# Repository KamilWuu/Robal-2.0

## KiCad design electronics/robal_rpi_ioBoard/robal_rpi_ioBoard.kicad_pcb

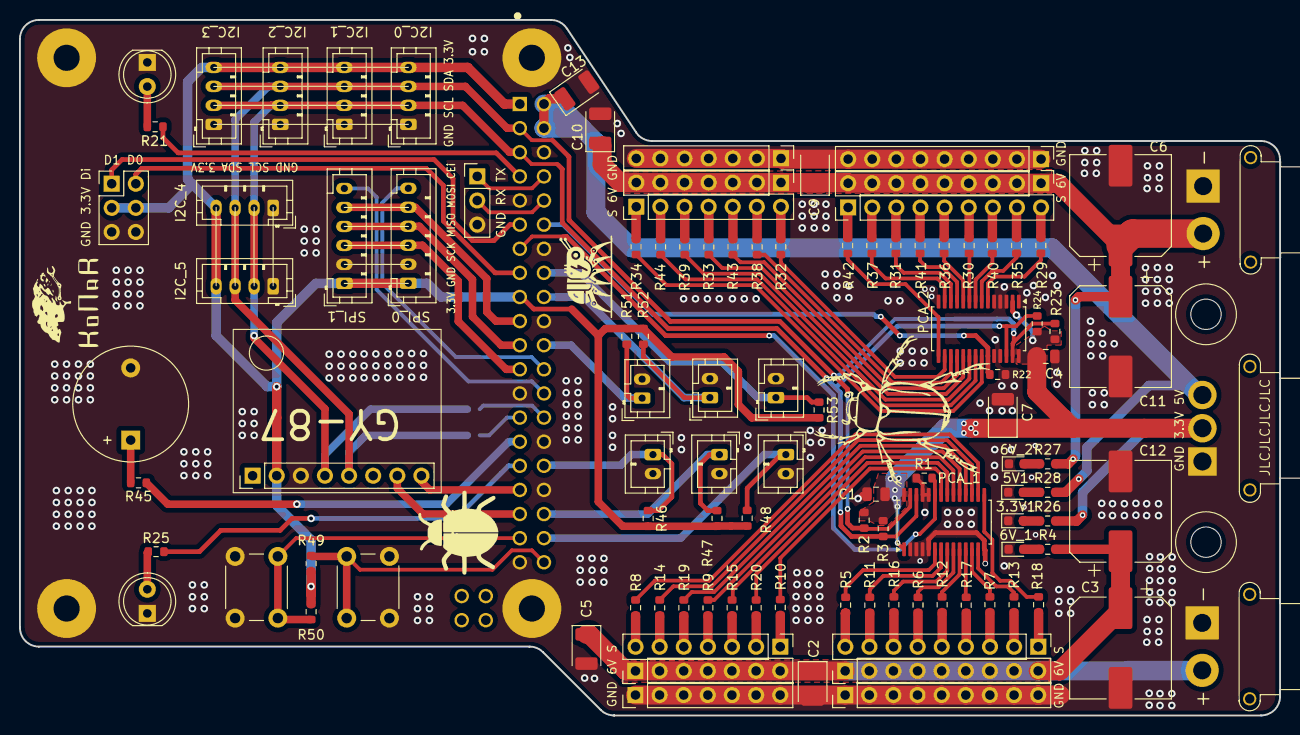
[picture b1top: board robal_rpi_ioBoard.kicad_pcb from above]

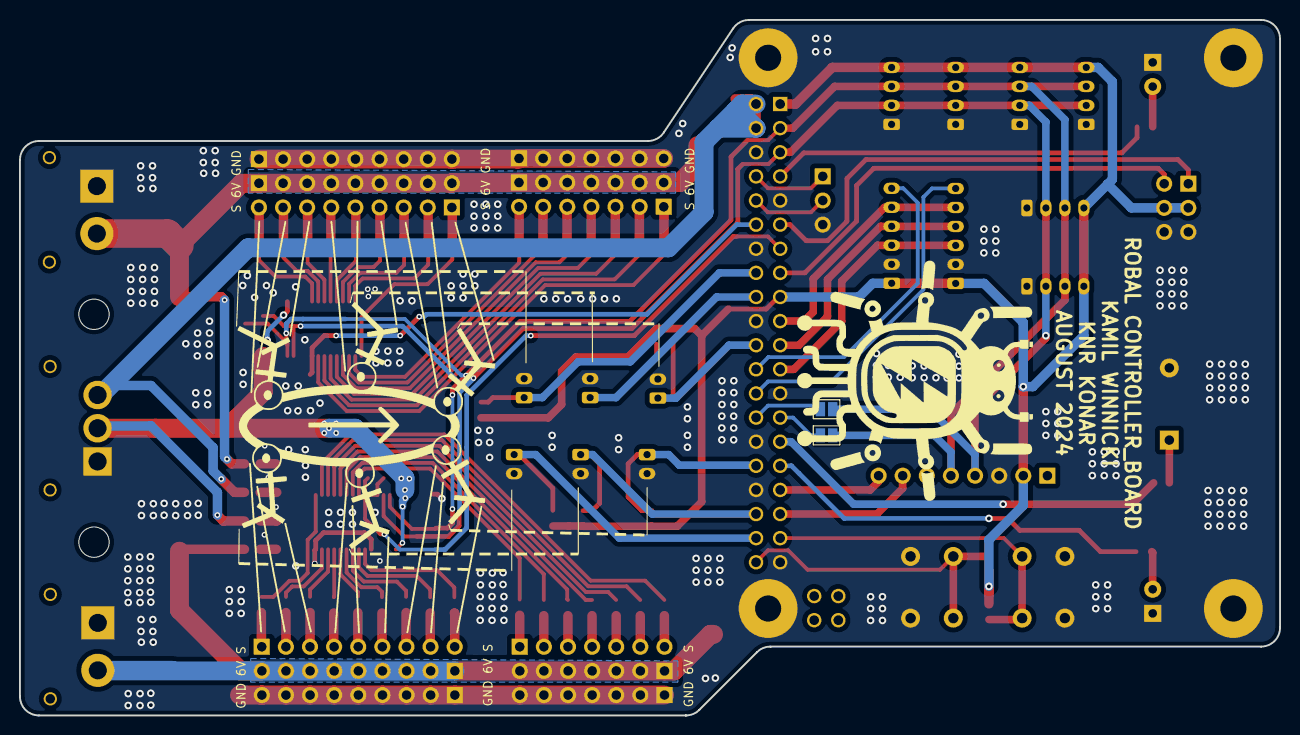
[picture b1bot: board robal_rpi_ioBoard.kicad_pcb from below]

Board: 2 copper layers, 132.7 x 73.2 mm, 111 parts (2 on the bottom side), 105 nets.

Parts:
3.3V1, 5V1, 6V_1, 6V_2: LED; LED_0603_1608Metric
BZ1: Buzzer; Buzzer_12x9.5RM7.6
C1, C4: 10uF; C_0805_2012Metric
C2, C5, C7, C9, C10, C13: >1mF; CP_EIA-3528-21_Kemet-B
C3, C6, C11, C12: >1mF; CP_Elec_10x10.5
D2, D7: LED; LED_D5.0mm
GY-87: GY-87
J1: Conn_01x03_Pin; PinHeader_1x03_P2.54mm_Vertical
J2, J3: Conn_01x02_Socket; AMASS_XT30PW-F_1x02_P2.50mm_Horizontal
J4: Conn_01x03_Socket; AMASS_MR30PW-FB_1x03_P3.50mm_Horizontal
J5, J6, J7, J8, J10, J11: Conn_01x04_Socket; JST_PH_B4B-PH-K_1x04_P2.00mm_Vertical
J9: Conn_02x03_Counter_Clockwise; PinHeader_2x03_P2.54mm_Vertical
JP1, JP2: Jumper_2_Open; SolderJumper-2_P1.3mm_Open_Pad1.0x1.5mm
PCA_1, PCA_2: PCA9685PW; TSSOP-28_4.4x9.7mm_P0.65mm
PCA_1_G_CONN1: PCA_1_G1; PinHeader_1x09_P2.54mm_Vertical
PCA_1_G_CONN2: PCA_1_G2; PinHeader_1x07_P2.54mm_Vertical
PCA_1_S_CONN1: PCA_1_S1; PinHeader_1x09_P2.54mm_Vertical
PCA_1_S_CONN2: PCA_1_S2; PinHeader_1x07_P2.54mm_Vertical
PCA_1_V_CONN1: PCA_1_V1; PinHeader_1x09_P2.54mm_Vertical
PCA_1_V_CONN2: PCA_1_V2; PinHeader_1x07_P2.54mm_Vertical
PCA_2_G_CONN1: PCA_2_G1; PinHeader_1x09_P2.54mm_Vertical
PCA_2_G_CONN2: PCA_2_G2; PinHeader_1x07_P2.54mm_Vertical
PCA_2_S_CONN1: PCA_2_S1; PinHeader_1x09_P2.54mm_Vertical
PCA_2_S_CONN2: PCA_2_S2; PinHeader_1x07_P2.54mm_Vertical
PCA_2_V_CONN1: PCA_2_V1; PinHeader_1x09_P2.54mm_Vertical
PCA_2_V_CONN2: PCA_2_V2; PinHeader_1x07_P2.54mm_Vertical
R1, R2, R3, R22, R23, R24, R46, R47, R48, R49, R50, R51, R52, R53: 10K; R_0603_1608Metric
R4, R27: 2K; R_0603_1608Metric
R5, R6, R7, R8, R9, R10, R11, R12, R13, R14, R15, R16, R17, R18, R19, R20, R29, R30, R31, R32, R33, R34, R35, R36, R37, R38, R39, R40, R41, R42, R43, R44: 220; R_0603_1608Metric
R21, R25, R26, R28: 500; R_0603_1608Metric
R45: 1K; R_0603_1608Metric
SPI_CONN0, SPI_CONN1: SPI_CONN; JST_PH_B6B-PH-K_1x06_P2.00mm_Vertical
SW1, SW2: SW_Omron_B3FS; SW_PUSH_6mm
TS_1, TS_2, TS_3, TS_4, TS_5, TS_6: TS_socket; JST_PH_B2B-PH-K_1x02_P2.00mm_Vertical
U1: RASPBERRY_PI_4B_4GB; MODULE_RASPBERRY_PI_4B_4GB

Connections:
+3.3V: C1.1, C4.1, C7.1, J4.2, PCA_1.1 (A0), PCA_1.28 (VDD), PCA_2.2 (A1), PCA_2.28 (VDD), R2.2, R3.1, R23.2, R24.1, R26.2
+3.3V_RP: GY-87.2 (3.3V), J5.4, J6.4, J7.4, J8.4, J9.3, J9.4, J10.4, J11.4, R46.2, R47.2, R48.2, R49.1, R50.1, R51.2, R52.2, R53.2, SPI_CONN0.1, SPI_CONN1.1, U1.1 (3V3), U1.17 (3V3)
+5V: C13.1, J4.3, R28.2, U1.2 (5V), U1.4 (5V)
+6V_1: C2.1, C3.1, C5.1, C12.1, J2.2, PCA_1_V_CONN1.1, PCA_1_V_CONN1.2, PCA_1_V_CONN1.3, PCA_1_V_CONN1.4, PCA_1_V_CONN1.5, PCA_1_V_CONN1.6, PCA_1_V_CONN1.7, PCA_1_V_CONN1.8, PCA_1_V_CONN1.9, PCA_1_V_CONN2.1, PCA_1_V_CONN2.2, PCA_1_V_CONN2.3, PCA_1_V_CONN2.4, PCA_1_V_CONN2.5, PCA_1_V_CONN2.6, PCA_1_V_CONN2.7, R4.2
+6V_2: C6.1, C9.1, C10.1, C11.1, J3.2, PCA_2_V_CONN1.1, PCA_2_V_CONN1.2, PCA_2_V_CONN1.3, PCA_2_V_CONN1.4, PCA_2_V_CONN1.5, PCA_2_V_CONN1.6, PCA_2_V_CONN1.7, PCA_2_V_CONN1.8, PCA_2_V_CONN1.9, PCA_2_V_CONN2.1, PCA_2_V_CONN2.2, PCA_2_V_CONN2.3, PCA_2_V_CONN2.4, PCA_2_V_CONN2.5, PCA_2_V_CONN2.6, PCA_2_V_CONN2.7, R27.2
BUZZ: R45.1, U1.29 (GPIO5)
D0: J9.2, U1.15 (GPIO22/GPIO_GEN3)
D1: J9.1, U1.11 (GPIO17/GPIO_GEN0)
DRDY: GY-87.8 (DRDY), U1.33 (GPIO13)
GND: 3.3V1.1 (K), 5V1.1 (K), 6V_1.1 (K), 6V_2.1 (K), BZ1.2 (-), C1.2, C2.2, C3.2, C4.2, C5.2, C6.2, C7.2, C9.2, C10.2, C11.2, C12.2, C13.2, D2.1 (K), D7.1 (K), GY-87.3 (GND), J1.3, J2.1, J3.1, J4.1, J5.1, J6.1, J7.1, J8.1, J9.5, J9.6, J10.1, J11.1, PCA_1.2 (A1), PCA_1.3 (A2), PCA_1.4 (A3), PCA_1.5 (A4), PCA_1.14 (VSS), PCA_1.24 (A5), PCA_1.25 (EXTCLK), PCA_1_G_CONN1.1, PCA_1_G_CONN1.2, PCA_1_G_CONN1.3, PCA_1_G_CONN1.4, PCA_1_G_CONN1.5, PCA_1_G_CONN1.6, PCA_1_G_CONN1.7, PCA_1_G_CONN1.8, PCA_1_G_CONN1.9, PCA_1_G_CONN2.1, PCA_1_G_CONN2.2, PCA_1_G_CONN2.3, PCA_1_G_CONN2.4, PCA_1_G_CONN2.5, PCA_1_G_CONN2.6, PCA_1_G_CONN2.7, PCA_2.1 (A0), PCA_2.3 (A2), PCA_2.4 (A3), PCA_2.5 (A4), PCA_2.14 (VSS), PCA_2.24 (A5), PCA_2.25 (EXTCLK), PCA_2_G_CONN1.1, PCA_2_G_CONN1.2, PCA_2_G_CONN1.3, PCA_2_G_CONN1.4, PCA_2_G_CONN1.5, PCA_2_G_CONN1.6, PCA_2_G_CONN1.7, PCA_2_G_CONN1.8, PCA_2_G_CONN1.9, PCA_2_G_CONN2.1, PCA_2_G_CONN2.2, PCA_2_G_CONN2.3, PCA_2_G_CONN2.4, PCA_2_G_CONN2.5, PCA_2_G_CONN2.6, PCA_2_G_CONN2.7, R1.2, R22.2, SPI_CONN0.2, SPI_CONN1.2, SW1.2, SW2.2, TS_1.2, TS_2.2, TS_3.2, TS_4.2, TS_5.2, TS_6.2, U1.6 (GND), U1.9 (GND), U1.14 (GND), U1.20 (GND), U1.25 (GND), U1.30 (GND), U1.34 (GND), U1.39 (GND), U1.S1 (SHIELD), U1.S2 (SHIELD), U1.S3 (SHIELD), U1.S4 (SHIELD)
I2C_SCL: GY-87.4 (SCL), J5.2, J6.2, J7.2, J8.2, J10.2, J11.2, JP2.1 (A), PCA_1.26 (SCL), PCA_2.26 (SCL), R3.2, R24.2, U1.5 (GPIO3/SCL1)
I2C_SDA: GY-87.5 (SDA), J5.3, J6.3, J7.3, J8.3, J10.3, J11.3, JP1.1 (A), PCA_1.27 (SDA), PCA_2.27 (SDA), R2.1, R23.1, U1.3 (GPIO2/SDA1)
INTA_MPU: GY-87.7 (INTA), U1.35 (GPIO19)
unnamed: 3.3V1.2 (A), R26.1
unnamed: 5V1.2 (A), R28.1
unnamed: 6V_1.2 (A), R4.1
unnamed: 6V_2.2 (A), R27.1
unnamed: BZ1.1 (+), R45.2
unnamed: D2.2 (A), R21.1
unnamed: D7.2 (A), R25.1
unnamed: JP1.2 (B), U1.27 (ID_SD)
unnamed: JP2.2 (B), U1.28 (ID_SC)
unnamed: PCA_1.6 (LED0), R5.1
unnamed: PCA_1.7 (LED1), R11.1
unnamed: PCA_1.8 (LED2), R16.1
unnamed: PCA_1.9 (LED3), R6.1
unnamed: PCA_1.10 (LED4), R12.1
unnamed: PCA_1.11 (LED5), R17.1
unnamed: PCA_1.12 (LED6), R7.1
unnamed: PCA_1.13 (LED7), R13.1
unnamed: PCA_1.15 (LED8), R18.1
unnamed: PCA_1.16 (LED9), R8.1
unnamed: PCA_1.17 (LED10), R14.1
unnamed: PCA_1.18 (LED11), R19.1
unnamed: PCA_1.19 (LED12), R9.1
unnamed: PCA_1.20 (LED13), R15.1
unnamed: PCA_1.21 (LED14), R20.1
unnamed: PCA_1.22 (LED15), R10.1
unnamed: PCA_1_S_CONN1.1, R18.2
unnamed: PCA_1_S_CONN1.2, R13.2
unnamed: PCA_1_S_CONN1.3, R7.2
unnamed: PCA_1_S_CONN1.4, R17.2
unnamed: PCA_1_S_CONN1.5, R12.2
unnamed: PCA_1_S_CONN1.6, R6.2
unnamed: PCA_1_S_CONN1.7, R16.2
unnamed: PCA_1_S_CONN1.8, R11.2
unnamed: PCA_1_S_CONN1.9, R5.2
unnamed: PCA_1_S_CONN2.1, R10.2
unnamed: PCA_1_S_CONN2.2, R20.2
unnamed: PCA_1_S_CONN2.3, R15.2
unnamed: PCA_1_S_CONN2.4, R9.2
unnamed: PCA_1_S_CONN2.5, R19.2
unnamed: PCA_1_S_CONN2.6, R14.2
unnamed: PCA_1_S_CONN2.7, R8.2
unnamed: PCA_2.6 (LED0), R29.1
unnamed: PCA_2.7 (LED1), R35.1
unnamed: PCA_2.8 (LED2), R40.1
unnamed: PCA_2.9 (LED3), R30.1
unnamed: PCA_2.10 (LED4), R36.1
unnamed: PCA_2.11 (LED5), R41.1
unnamed: PCA_2.12 (LED6), R31.1
unnamed: PCA_2.13 (LED7), R37.1
unnamed: PCA_2.15 (LED8), R42.1
unnamed: PCA_2.16 (LED9), R32.1
unnamed: PCA_2.17 (LED10), R38.1
unnamed: PCA_2.18 (LED11), R43.1
unnamed: PCA_2.19 (LED12), R33.1
unnamed: PCA_2.20 (LED13), R39.1
unnamed: PCA_2.21 (LED14), R44.1
unnamed: PCA_2.22 (LED15), R34.1
unnamed: PCA_2_S_CONN1.1, R42.2
unnamed: PCA_2_S_CONN1.2, R37.2
unnamed: PCA_2_S_CONN1.3, R31.2
unnamed: PCA_2_S_CONN1.4, R41.2
unnamed: PCA_2_S_CONN1.5, R36.2
unnamed: PCA_2_S_CONN1.6, R30.2
unnamed: PCA_2_S_CONN1.7, R40.2
unnamed: PCA_2_S_CONN1.8, R35.2
unnamed: PCA_2_S_CONN1.9, R29.2
unnamed: PCA_2_S_CONN2.1, R34.2
unnamed: PCA_2_S_CONN2.2, R44.2
unnamed: PCA_2_S_CONN2.3, R39.2
unnamed: PCA_2_S_CONN2.4, R33.2
unnamed: PCA_2_S_CONN2.5, R43.2
unnamed: PCA_2_S_CONN2.6, R38.2
unnamed: PCA_2_S_CONN2.7, R32.2
PCA_1_OE: PCA_1.23 (~OE), R1.1, U1.13 (GPIO27/GPIO_GEN2)
PCA_2_OE: PCA_2.23 (~OE), R22.1, U1.12 (GPIO18/GPIO_GEN1)
SPI_CE0: SPI_CONN0.6, U1.24 (GPIO8/~SPI_CE0)
SPI_CE1: SPI_CONN1.6, U1.26 (GPIO7/~SPI_CE1)
SPI_MISO: SPI_CONN0.4, SPI_CONN1.4, U1.21 (GPIO9/SPI_MISO)
SPI_MOSI: SPI_CONN0.5, SPI_CONN1.5, U1.19 (GPIO10/SPI_MOSI)
SPI_SCLK: SPI_CONN0.3, SPI_CONN1.3, U1.23 (GPIO11/SPI_SCLK)
TS_1: R46.1, TS_1.1, U1.32 (GPIO12)
TS_2: R51.1, TS_4.1, U1.22 (GPIO25/GPIO_GEN6)
TS_3: R47.1, TS_2.1, U1.36 (GPIO16)
TS_4: R52.1, TS_5.1, U1.18 (GPIO24/GPIO_GEN5)
TS_5: R48.1, TS_3.1, U1.38 (GPIO20)
TS_6: R53.1, TS_6.1, U1.16 (GPIO23/GPIO_GEN4)
UART_RX: J1.2, U1.10 (GPIO15/RXD0)
UART_TX: J1.1, U1.8 (GPIO14/TXD0)
U_BUTTON1: R49.2, SW1.1, U1.40 (GPIO21)
U_BUTTON2: R50.2, SW2.1, U1.37 (GPIO26)
U_LED1: R25.2, U1.31 (GPIO6)
U_LED2: R21.2, U1.7 (GPIO4/GPIO_GCKL)

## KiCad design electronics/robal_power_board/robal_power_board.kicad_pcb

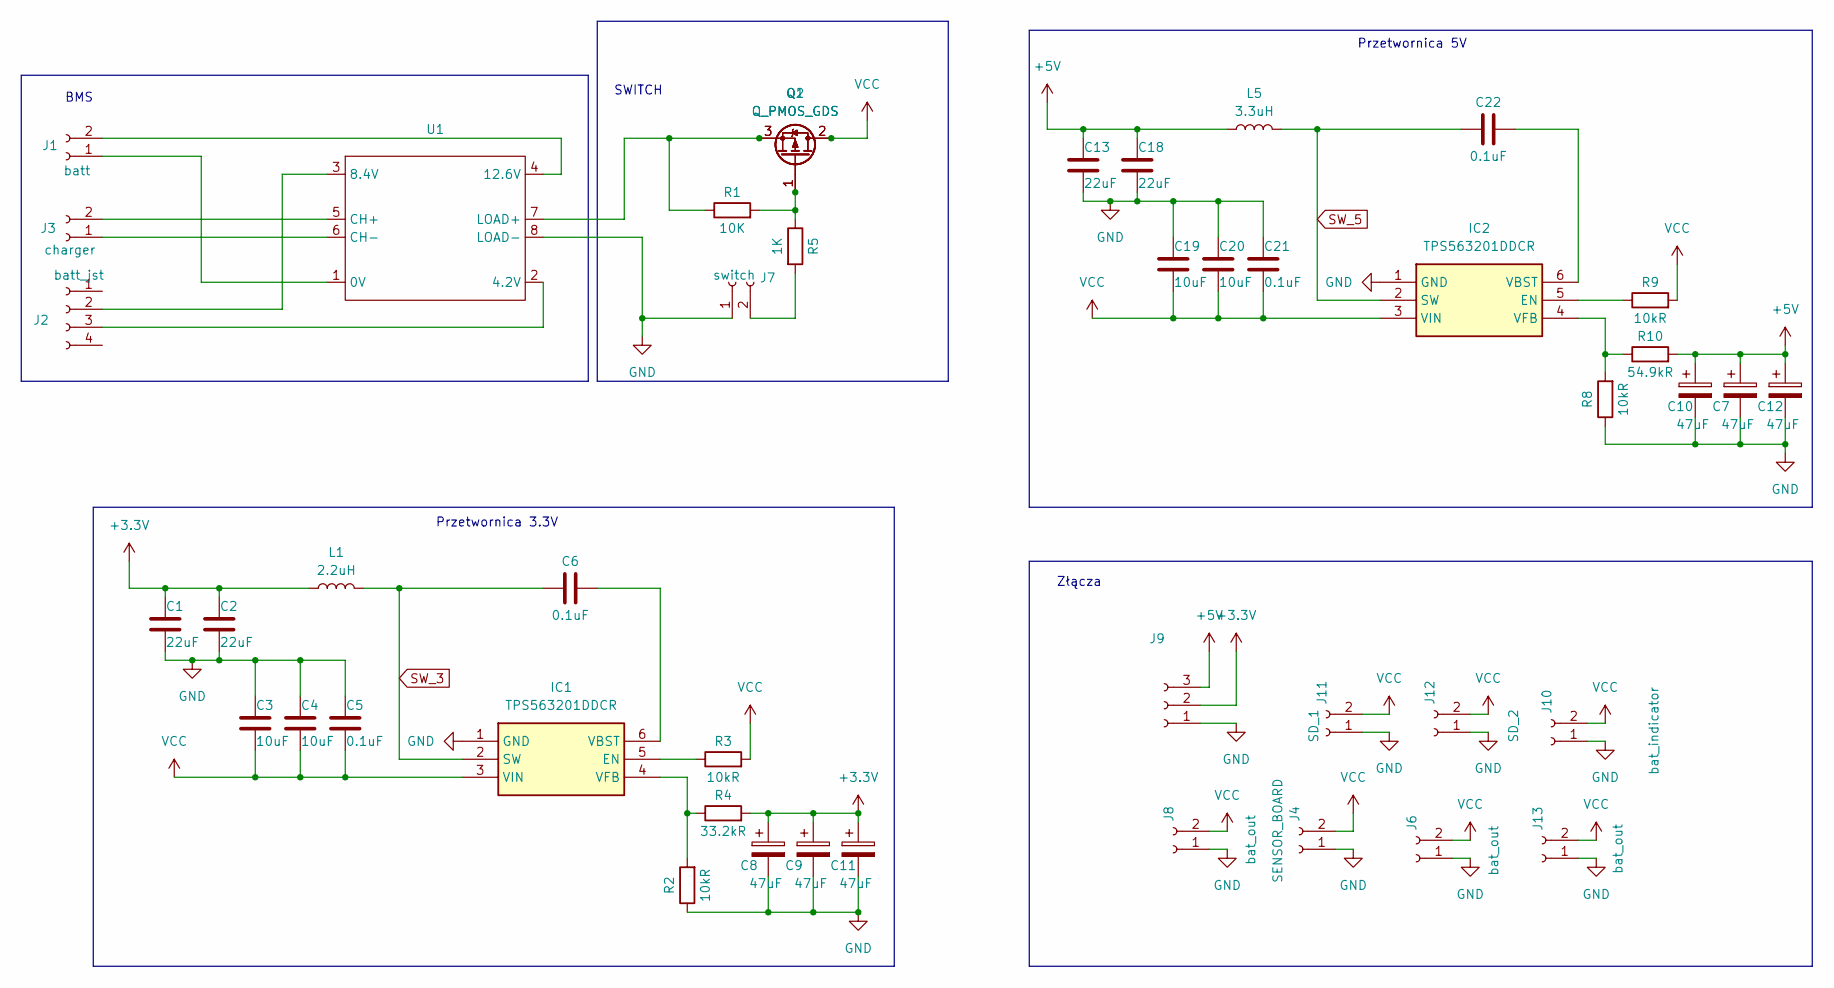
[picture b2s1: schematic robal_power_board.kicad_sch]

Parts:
C1, C2, C13, C18: 22uF; C_0805_2012Metric
C3, C4, C19, C20: 10uF; C_0805_2012Metric
C5, C6, C21, C22: 0.1uF; C_0603_1608Metric
C7, C8, C9, C10, C11, C12: 47uF; CP_EIA-3528-21_Kemet-B_Pad1.50x2.35mm_HandSolder
IC1, IC2: TPS563201DDCR; SOT-23-6; Manufacturer_Part_Number TPS563201DDCR
J1: batt; AMASS_XT60PW-M_1x02_P7.20mm_Horizontal
J2: batt_jst; JST_XH_S4B-XH-A_1x04_P2.50mm_Horizontal
J3: charger; AMASS_XT30PW-F_1x02_P2.50mm_Horizontal
J4: SENSOR_BOARD; AMASS_XT30PW-F_1x02_P2.50mm_Horizontal
J6, J8, J13: bat_out; JST_PH_B2B-PH-K_1x02_P2.00mm_Vertical
J7: switch; JST_PH_B2B-PH-K_1x02_P2.00mm_Vertical
J9: Conn_01x03_Socket; AMASS_MR30PW-FB_1x03_P3.50mm_Horizontal
J10: bat_indicator; JST_PH_B2B-PH-K_1x02_P2.00mm_Vertical
J11: SD_1; AMASS_XT30PW-F_1x02_P2.50mm_Horizontal
J12: SD_2; AMASS_XT30PW-F_1x02_P2.50mm_Horizontal
L1: 2.2uH; L_Bourns_SRP7028A_7.3x6.6mm
L5: 3.3uH; L_SXN_SMDRI125
Q1, Q2: Q_PMOS_GDS; DFN5X6_AON6403
R1: 10K; R_0603_1608Metric
R2, R3, R8, R9: 10kR; R_0603_1608Metric
R4: 33.2kR; R_0603_1608Metric
R5: 1K; R_0603_1608Metric
R10: 54.9kR; R_0603_1608Metric
U1: 3S_BMS

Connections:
+3.3V: C1.2, C2.2, C8.1, C9.1, C11.1, J9.2, L1.1, R4.2
+5V: C7.1, C10.1, C12.1, C13.2, C18.2, J9.3, L5.1, R10.2
GND: C1.1, C2.1, C3.2, C4.2, C5.2, C7.2, C8.2, C9.2, C10.2, C11.2, C12.2, C13.1, C18.1, C19.2, C20.2, C21.2, IC1.1 (GND), IC2.1 (GND), J4.1, J6.1, J7.1, J8.1, J9.1, J10.1, J11.1, J12.1, J13.1, R2.1, R8.1, U1.8 (LOAD-); also elsewhere on the board
unnamed: IC1.5 (EN), R3.1
unnamed: C6.2, IC1.6 (VBST)
unnamed: IC1.4 (VFB), R2.2, R4.1
unnamed: IC2.5 (EN), R9.1
unnamed: C22.2, IC2.6 (VBST)
unnamed: IC2.4 (VFB), R8.2, R10.1
unnamed: J1.1, U1.1 (0V)
unnamed: J1.2, U1.4 (12.6V)
unnamed: J2.2, U1.3 (8.4V)
unnamed: J2.3, U1.2 (4.2V)
unnamed 13: J3.1, U1.6 (CH-); also elsewhere on the board
unnamed 14: J3.2, U1.5 (CH+); also elsewhere on the board
unnamed 15: J7.2, R5.2; also elsewhere on the board
unnamed: Q1.1 (G), Q2.1 (G), R1.2, R5.1
unnamed: Q1.3 (S), Q2.3 (S), R1.1, U1.7 (LOAD+)
SW_3: C6.1, IC1.2 (SW), L1.2
SW_5: C22.1, IC2.2 (SW), L5.2
VCC: C3.1, C4.1, C5.1, C19.1, C20.1, C21.1, IC1.3 (VIN), IC2.3 (VIN), J4.2, J6.2, J8.2, J10.2, J11.2, J12.2, J13.2, Q1.2 (D), Q2.2 (D), R3.2, R9.2; also elsewhere on the board

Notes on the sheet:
BMS
Złącza
Przetwornica 5V
SWITCH
Przetwornica 3.3V

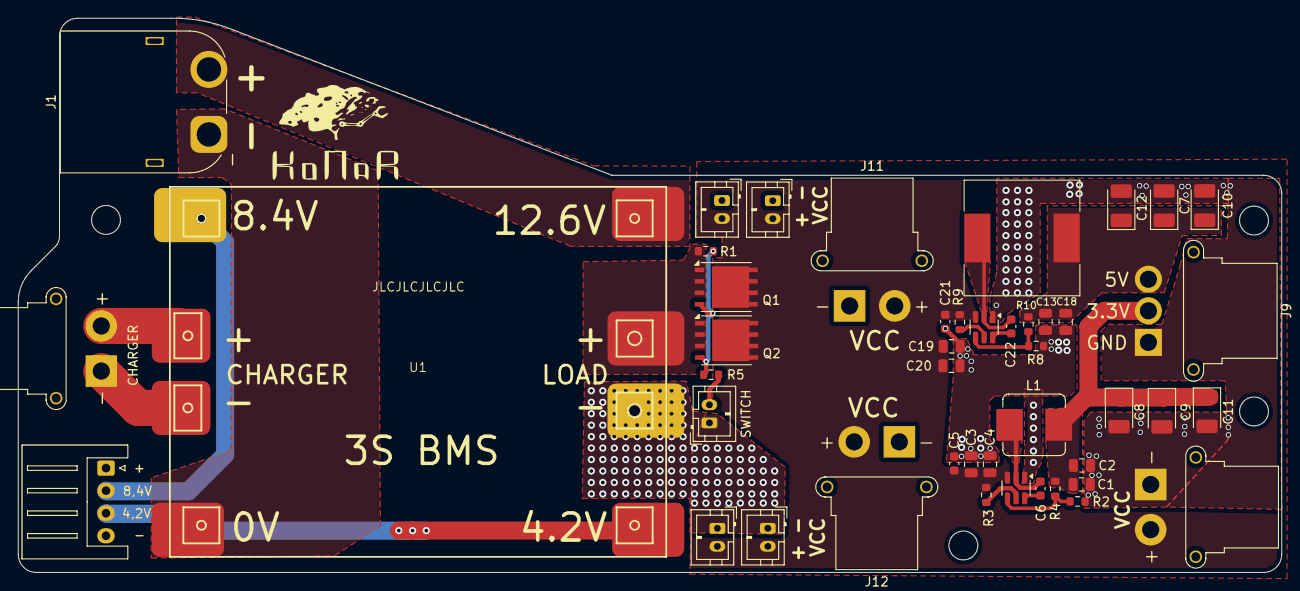
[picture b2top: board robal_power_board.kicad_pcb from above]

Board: 2 copper layers, 140.0 x 61.4 mm, 45 parts (0 on the bottom side), 21 nets.

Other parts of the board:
CHARGER: charger; AMASS_XT30PW-F_1x02_P2.50mm_Horizontal
SENSOR_BOARD: SENSOR_BOARD; AMASS_XT30PW-F_1x02_P2.50mm_Horizontal
SWITCH: switch; JST_PH_B2B-PH-K_1x02_P2.00mm_Vertical

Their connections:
GND: SENSOR_BOARD.1, SWITCH.1; also elsewhere on the board
unnamed 13: CHARGER.1; also elsewhere on the board
unnamed 14: CHARGER.2; also elsewhere on the board
unnamed 15: SWITCH.2; also elsewhere on the board
VCC: SENSOR_BOARD.2; also elsewhere on the board

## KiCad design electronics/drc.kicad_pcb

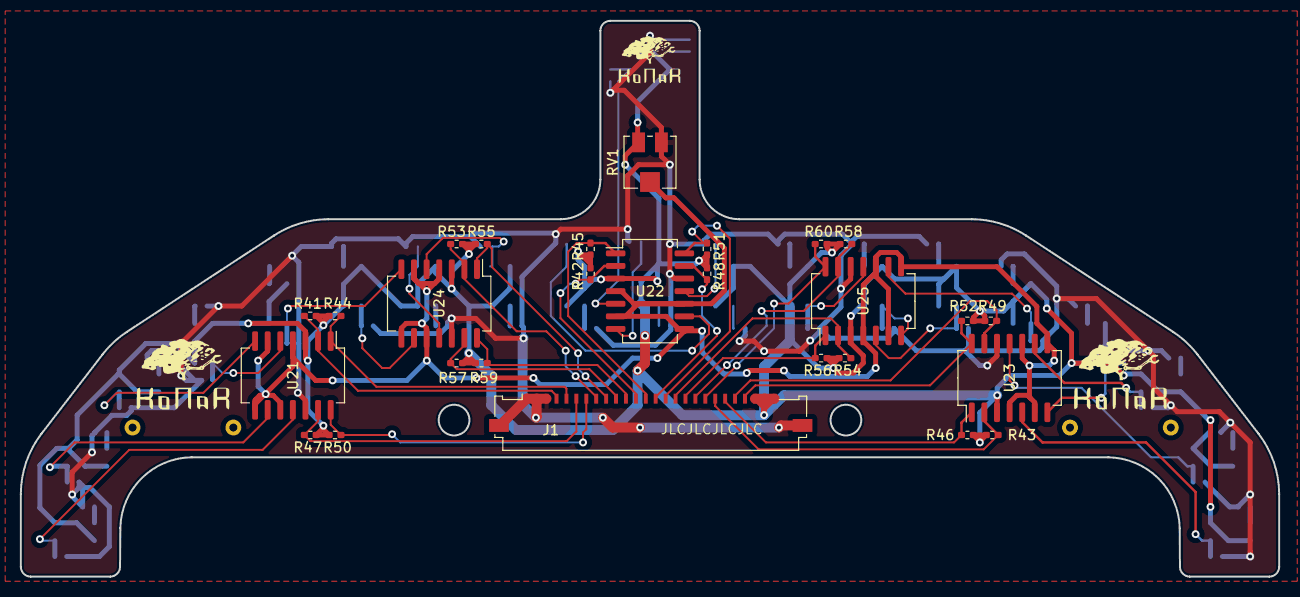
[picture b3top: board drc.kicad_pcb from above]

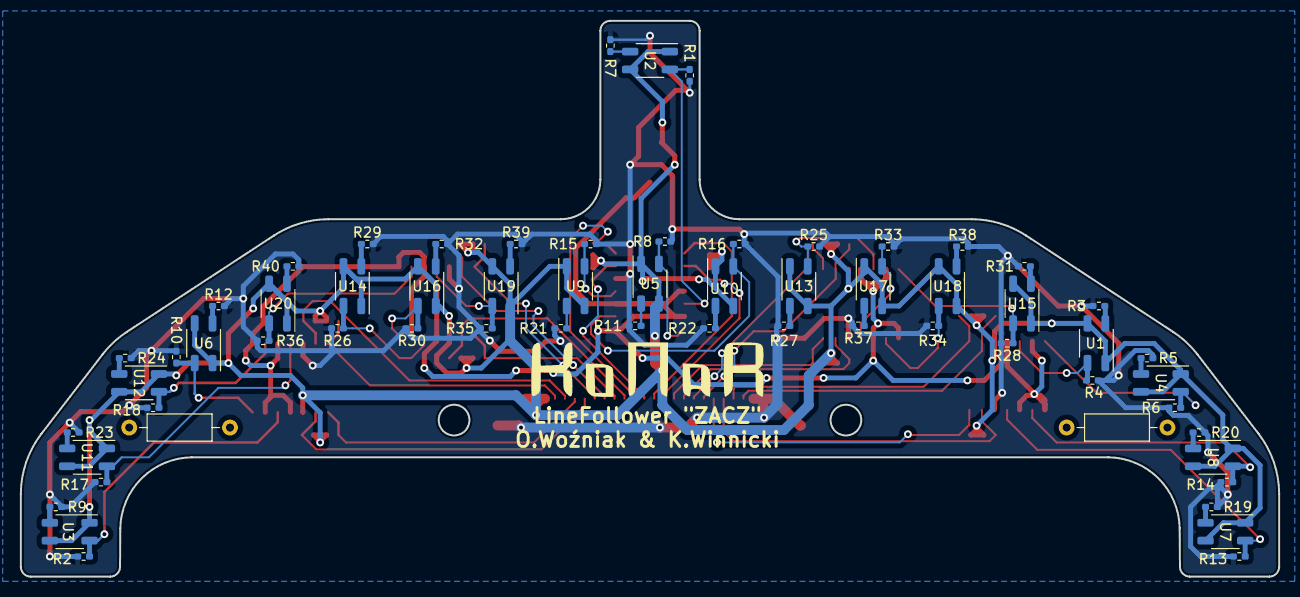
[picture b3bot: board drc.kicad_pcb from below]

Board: 2 copper layers, 126.8 x 56.0 mm, 89 parts (62 on the bottom side), 63 nets.

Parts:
J1: Conn_01x26_Socket; Molex_200528-0260_1x26-1MP_P1.00mm_Horizontal
R1, R2, R4, R6, R8, R10, R13, R14, R15, R16, R17, R18, R25, R26, R28, R30, R33, R34, R35, R36: 22kR; R_0402_1005Metric_Pad0.72x0.64mm_HandSolder
R3, R5, R7, R9, R11, R12, R19, R20, R21, R22, R23, R24, R27, R29, R31, R32, R37, R38, R39, R40: 110R; R_0402_1005Metric_Pad0.72x0.64mm_HandSolder
R41, R42, R43, R44, R45, R46, R47, R48, R49, R50, R51, R52, R53, R54, R55, R56, R57, R58, R59, R60: 15kR; R_0402_1005Metric_Pad0.72x0.64mm_HandSolder
R61, R62: R; R_Axial_DIN0207_L6.3mm_D2.5mm_P10.16mm_Horizontal
RV1: R_Potentiometer; Potentiometer_Vishay_TS53YJ_Vertical
U1, U2, U3, U4, U5, U6, U7, U8, U9, U10, U11, U12, U13, U14, U15, U16, U17, U18, U19, U20: ITR8307-S17-TR8; Everlight_ITR1201SR10AR
U21, U22, U23, U24, U25: LM2901; SO-14_5.3x10.2mm_P1.27mm

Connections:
+3.3V: J1.24, J1.25, J1.26, R41.1, R42.1, R43.1, R44.1, R45.1, R46.1, R47.1, R48.1, R49.1, R50.1, R51.1, R52.1, R53.1, R54.1, R55.1, R56.1, R57.1, R58.1, R59.1, R60.1, RV1.1, U1.2 (A), U1.3, U2.2 (A), U2.3, U3.2 (A), U3.3, U4.2 (A), U4.3, U5.2 (A), U5.3, U6.2 (A), U6.3, U7.2 (A), U7.3, U8.2 (A), U8.3, U9.2 (A), U9.3, U10.2 (A), U10.3, U11.2 (A), U11.3, U12.2 (A), U12.3, U13.2 (A), U13.3, U14.2 (A), U14.3, U15.2 (A), U15.3, U16.2 (A), U16.3, U17.2 (A), U17.3, U18.2 (A), U18.3, U19.2 (A), U19.3, U20.2 (A), U20.3, U21.3 (V+), U22.3 (V+), U23.3 (V+), U24.3 (V+), U25.3 (V+)
DETECT_01: J1.4, R41.2, U21.2
DETECT_02: J1.5, R44.2, U21.1
DETECT_03: J1.6, R47.2, U21.13
DETECT_04: J1.7, R50.2, U21.14
DETECT_05: J1.8, R53.2, U24.2
DETECT_06: J1.9, R55.2, U24.1
DETECT_07: J1.10, R57.2, U24.13
DETECT_08: J1.11, R59.2, U24.14
DETECT_09: J1.12, R42.2, U22.2
DETECT_10: J1.13, R45.2, U22.1
DETECT_11: J1.14, R48.2, U22.13
DETECT_12: J1.15, R51.2, U22.14
DETECT_13: J1.16, R54.2, U25.2
DETECT_14: J1.17, R56.2, U25.1
DETECT_15: J1.18, R58.2, U25.13
DETECT_16: J1.19, R60.2, U25.14
DETECT_17: J1.20, R43.2, U23.2
DETECT_18: J1.21, R46.2, U23.1
DETECT_19: J1.22, R49.2, U23.13
DETECT_20: J1.23, R52.2, U23.14
GND: J1.1, J1.2, J1.3, R1.2, R2.2, R3.2, R4.2, R5.2, R6.2, R7.2, R8.2, R9.2, R10.2, R11.2, R12.2, R13.2, R14.2, R15.2, R16.2, R17.2, R18.2, R19.2, R20.2, R21.2, R22.2, R23.2, R24.2, R25.2, R26.2, R27.2, R28.2, R29.2, R30.2, R31.2, R32.2, R33.2, R34.2, R35.2, R36.2, R37.2, R38.2, R39.2, R40.2, RV1.3, U21.12 (V-), U22.12 (V-), U23.12 (V-), U24.12 (V-), U25.12 (V-)
unnamed: R3.1, U1.1 (K)
unnamed: R7.1, U2.1 (K)
unnamed: R9.1, U3.1 (K)
unnamed: R5.1, U4.1 (K)
unnamed: R11.1, U5.1 (K)
unnamed: R12.1, U6.1 (K)
unnamed: R19.1, U7.1 (K)
unnamed: R20.1, U8.1 (K)
unnamed: R21.1, U9.1 (K)
unnamed: R22.1, U10.1 (K)
unnamed: R23.1, U11.1 (K)
unnamed: R24.1, U12.1 (K)
unnamed: R27.1, U13.1 (K)
unnamed: R29.1, U14.1 (K)
unnamed: R31.1, U15.1 (K)
unnamed: R32.1, U16.1 (K)
unnamed: R37.1, U17.1 (K)
unnamed: R38.1, U18.1 (K)
unnamed: R39.1, U19.1 (K)
unnamed: R40.1, U20.1 (K)
SIGNAL_IR_01: R4.1, U1.4, U21.5 (+)
SIGNAL_IR_02: R6.1, U4.4, U21.7 (+)
SIGNAL_IR_03: R13.1, U7.4, U21.11 (+)
SIGNAL_IR_04: R14.1, U8.4, U21.9 (+)
SIGNAL_IR_05: R25.1, U13.4, U24.5 (+)
SIGNAL_IR_06: R28.1, U15.4, U24.7 (+)
SIGNAL_IR_07: R33.1, U17.4, U24.11 (+)
SIGNAL_IR_08: R34.1, U18.4, U24.9 (+)
SIGNAL_IR_09: R1.1, U2.4, U22.5 (+)
SIGNAL_IR_10: R8.1, U5.4, U22.7 (+)
SIGNAL_IR_11: R15.1, U9.4, U22.11 (+)
SIGNAL_IR_12: R16.1, U10.4, U22.9 (+)
SIGNAL_IR_13: R26.1, U14.4, U25.5 (+)
SIGNAL_IR_14: R30.1, U16.4, U25.7 (+)
SIGNAL_IR_15: R35.1, U19.4, U25.11 (+)
SIGNAL_IR_16: R36.1, U20.4, U25.9 (+)
SIGNAL_IR_17: R2.1, U3.4, U23.5 (+)
SIGNAL_IR_18: R10.1, U6.4, U23.7 (+)
SIGNAL_IR_19: R17.1, U11.4, U23.11 (+)
SIGNAL_IR_20: R18.1, U12.4, U23.9 (+)
V_REF_IR: RV1.2, U21.4 (-), U21.6 (-), U21.8 (-), U21.10 (-), U22.4 (-), U22.6 (-), U22.8 (-), U22.10 (-), U23.4 (-), U23.6 (-), U23.8 (-), U23.10 (-), U24.4 (-), U24.6 (-), U24.8 (-), U24.10 (-), U25.4 (-), U25.6 (-), U25.8 (-), U25.10 (-)

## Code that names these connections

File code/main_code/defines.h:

#ifndef DEFINES_H
#define DEFINES_H

#include <stdio.h>
#include <wiringPi.h>
#include <stdbool.h>

/* ============================= OUTPUTS ============================= */
#define LED_RED     6
#define LED_GREEN   4
#define BUZZER      5

#define D_0         22
#define D_1         17

#define PCA_1_OE    27
#define PCA_2_OE    18
/* =========================== END OF OUTPUTS ========================= */

/* ============================= INPUTS ============================== */
#define TOUCH_SENSOR_1 12
#define TOUCH_SENSOR_2 25
#define TOUCH_SENSOR_3 16
#define TOUCH_SENSOR_4 24
#define TOUCH_SENSOR_5 20
#define TOUCH_SENSOR_6 23

#define TOUCH_SENSOR_LEFT_FRONT     TOUCH_SENSOR_1
#define TOUCH_SENSOR_LEFT_MIDDLE    TOUCH_SENSOR_3
#define TOUCH_SENSOR_LEFT_BACK      TOUCH_SENSOR_5

#define TOUCH_SENSOR_RIGHT_FRONT    TOUCH_SENSOR_2
#define TOUCH_SENSOR_RIGHT_MIDDLE   TOUCH_SENSOR_4
#define TOUCH_SENSOR_RIGHT_BACK     TOUCH_SENSOR_6

#define BUTTON_1    21
#define BUTTON_2    26

#define INTA_MPU    19
#define DRDY        13
/* =========================== END OF INPUTS ========================== */

/* ========================== COMMUNICATION ========================== */
#define SPI_CEO0    8
#define SPI_CEO1    7
#define SPI_SCLK    11
#define SPI_MOSI    10
#define SPI_MISO    9

#define I2C_SDA     2
#define I2C_SCL     3

#define TX          14
#define RX          15
/* ======================= END OF COMMUNICATION ======================= */

/* =========================== DEVICE ADDRESSES ======================= */
#define PCA_ADDRESS_LEFT    0x41
#define PCA_ADDRESS_RIGHT   0x42
#define MPU6050_ADDRESS     0x68
#define QMC5883L_ADDRESS    0x70
#define BMP180_ADDRESS      0x77
/* ===================== END OF DEVICE ADDRESSES ====================== */

/* ========================= Q INDEX ================================== */

#define LEFT_FRONT_Q1   2
#define LEFT_FRONT_Q2   1
#define LEFT_FRONT_Q3   0

#define LEFT_MIDDLE_Q1  5
#define LEFT_MIDDLE_Q2  15
#define LEFT_MIDDLE_Q3  3

#define LEFT_BACK_Q1    8
#define LEFT_BACK_Q2    7
#define LEFT_BACK_Q3    6    


#define RIGHT_FRONT_Q1  6
#define RIGHT_FRONT_Q2  7
#define RIGHT_FRONT_Q3  8

#define RIGHT_MIDDLE_Q1 3
#define RIGHT_MIDDLE_Q2 4
#define RIGHT_MIDDLE_Q3 5

#define RIGHT_BACK_Q1   0      
#define RIGHT_BACK_Q2   1 
#define RIGHT_BACK_Q3   2
/* ============================= END OF Q INDEX ====================== */







void StartGPIO()
{
    // Ustawienie GPIO na schemat numeracji Broadcom (BCM)
    wiringPiSetupGpio();

    /* =========================== OUTPUTS =========================== */
    pinMode(LED_RED, OUTPUT);
    //pinMode(LED_GREEN, OUTPUT);
    pinMode(BUZZER, OUTPUT);

    pinMode(D_0, OUTPUT);
    pinMode(D_1, OUTPUT);

    pinMode(PCA_1_OE, OUTPUT);
    pinMode(PCA_2_OE, OUTPUT);

    /* ============================ INPUTS =========================== */
    pinMode(TOUCH_SENSOR_1, INPUT);
    pinMode(TOUCH_SENSOR_2, INPUT);
    pinMode(TOUCH_SENSOR_3, INPUT);
    pinMode(TOUCH_SENSOR_4, INPUT);
    pinMode(TOUCH_SENSOR_5, INPUT);
    pinMode(TOUCH_SENSOR_6, INPUT);

    pinMode(BUTTON_1, INPUT);
    pinMode(BUTTON_2, INPUT);

    pinMode(INTA_MPU, INPUT);
    pinMode(DRDY, INPUT);

    /* ========================= COMMUNICATION ======================== */
    // SPI and I2C pins are often managed by the system driver and may not need manual configuration.
    // However, set their mode if manual configuration is required:

    /*

    pinMode(SPI_CEO0, OUTPUT);  // SPI Chip Enable 0
    pinMode(SPI_CEO1, OUTPUT);  // SPI Chip Enable 1
    pinMode(SPI_SCLK, OUTPUT);  // SPI Clock
    pinMode(SPI_MOSI, OUTPUT);  // SPI Master Out Slave In
    pinMode(SPI_MISO, INPUT);   // SPI Master In Slave Out

    pinMode(I2C_SDA, INPUT);    // I2C Data
    pinMode(I2C_SCL, INPUT);    // I2C Clock

    pinMode(TX, OUTPUT);        // UART TX
    pinMode(RX, INPUT);         // UART RX

    */

    /* ==================== Initial States for Outputs =================== */
    digitalWrite(LED_RED, LOW);
    //digitalWrite(LED_GREEN, LOW);
    digitalWrite(BUZZER, LOW);
    digitalWrite(D_0, LOW);
    digitalWrite(D_1, LOW);
    digitalWrite(PCA_1_OE, LOW);
    digitalWrite(PCA_2_OE, LOW);

   // printf("GPIO succesfully started!\n");
}

#endif // DEFINES_H

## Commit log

2024-06-27 utworzono repozytorium
2024-07-04 utworzono wstepny projekt nóg i glownej konstrukcji nośnej
2024-07-04 zaktualizowano liste czesci
2024-07-04 utworzono wstępny schemat plytki glownej
2024-07-05 dodano wiecej zlacz dla i2c
2024-07-06 rozpoczeto schemat plytki zasilania
2024-07-06 dokonczono wstepny schemat plytki zasilajacej
2024-07-07 drobne zmiany
2024-07-07 utworzono wstepny layout plytki zasilania
2024-07-08 zmiany w layoucie
2024-07-09 dodano mosfet
2024-07-09 ukonczono pierwsza wersje layoutu na power board
2024-07-11 poprawiono layout przetwornicy
2024-07-13 dodano nowa przetwornice, zmieniono layout
2024-07-21 zmiany w mechanice
2024-07-22 zmieniono montaz orczykow
2024-07-23 poprawiono 2 i 3 czlon
2024-07-24 zmiany w uchwycie serw
2024-07-25 zmieniono przetwornice na 5V
2024-07-27 nowa wersja plytki zasilania wersja nie pamietam ktora
2024-07-28 rozmieszczenie sekcji zasilania w robocie
2024-07-31 pierwsza skonczona wersja obudowy
2024-07-31 poprawki w uchwytach serw
2024-07-31 zmiany zmiany gotowy 1 czlon
2024-08-02 zmiany w ostatnim czlonie
2024-08-02 NOGI SKONCZONE
2024-08-04 prace nad plytka zasilania
2024-08-08 fix2
2024-08-11 plytka sterujaca prawie skonczona
2024-08-12 plytka sterujaca wstepnie skonczona
2024-08-17 plytki wstepnie gotowe do produkcji
2024-08-18 poprawki w elektronice 1
2024-09-15 export 3d models
2024-09-15 export 3d models2
2024-09-15 uchwyt na eletronike
2024-10-12 dodano plik dla kodu
2024-10-12 zmieniony tylny panel
2024-10-12 test gita z raspberki
2024-10-12 test2
2024-10-12 test3
2024-10-12 test 4
2024-10-12 testy obslugi pada od xboxa
2024-10-12 dodano testy i2c
2024-10-12 zmiany w strukturze plikow
2024-10-12 utworzono zalazek glownego kodu
2024-10-12 dodano defint touch sensors
2024-10-13 uwotrzono rysunki mechaniki i obrazki elektroniki
2024-10-13 wstepne funkcje sterowania serwami
2024-10-14 fix3
2024-10-15 ROBAL WSTALgit add .git add .
2024-10-16 fix21342
2024-10-16 dodano kilka pozytecznych programow
2024-10-18 poprawiono schematy
2024-10-18 przerobiono panel tylny
2024-10-20 utworzono szkielet kodu w posatci struktur dla nog i serw
2024-10-21 kod23123
2024-10-22 zaimplementowano kinematyke odwrotna
2024-10-22 prawdopodobnie naprawiono blad w kinematyce
2024-10-22 strona lewa dziala ale za to innego sie popsulo
2024-10-22 kinematyka-teraz bedzie dzialac!
2024-10-22 ROBOT WSTAJE NA KINEMATYCE!
2024-10-24 12345
2024-10-25 cos tam dziala
2024-10-26 poczatek faz chodu
2024-10-27 dodano pokrywe i naprawa gita
2024-10-28 ROBOT CHODZIgit add .git add .git add .git add .git add .git add .git add .git add .git add .git add .git add . : )
2024-10-29 edytowano podstawe i gore
2024-11-01 wprowadzono poruszanie sie za pomocą elips, retrakcja i protrakcja jednoczesnie
2024-11-01 elipsy dzialają, jednak dwa niesforne serwa stwarzają problemy
2024-11-01 robot chodzi ale dla zbyt wysokiej predkosci robi sie z = nan oraz step time nie dziala prawidlowo
2024-11-02 Dodano warunki sprawdzające w liczeniu z dla elipsy
2024-11-02 wprowadzono system sprawdzania bledow i aktualnej pozycji nog, co sprawilo ze robot chodzi w oparciu o elipsy
2024-11-09 robot sterowany z pilota
2024-11-12 dostrojenie chodu na Kraków
2024-11-12 dodano macierz transformacji
2024-11-12 macierze transformacji2
2024-11-15 dodano przeksztalcenia ukladow
2024-11-16 test jakobianu 1
2024-11-16 zabawy z jakobianem
2024-11-16 zabawy z jakobianem2
2024-11-17 poczatek nowej wersji kodu
2024-11-17 przygotowanie pod jacobian
2024-11-19 liczenie predkosci
2024-11-19 jakobian testy 2
2024-11-19 jakobian3
2024-11-20 program tetsowy do jakobianu - dla duzych predkosci bledy
2024-11-22 jacobian wkoncu dziala!
2024-11-22 dodano zapis wyników do csv
2024-11-22 test export
2024-11-22 test export2
2024-11-22 test export3
2024-11-22 test export4
2024-11-22 test export5
2024-11-23 testy zadajnika predkosci
2024-11-23 utworzono robal.c i dodano szkielet petli do kontrolera
2024-11-24 wstepny szkielet kodu
2024-11-24 dziala cos
2024-11-25 rozpoczeto refaktoryzacje struktur
2024-11-25 refraktor2
2024-11-27 kolejny refaktor kodu
2024-11-27 cos tam dziala ale są duże niedokladności
2024-11-29 naprawiono blad z bledna iteracja czasu - dziala jako tako w sumie git
2024-11-29 naprawiono blad z bledna iteracja czasu - dziala jako tako w sumie git 2
2024-11-29 testy z kontrolerrem
2024-11-29 teoretycznie robot jest sterowalny z pilota!
2024-11-29 dodano wyswietlanie katow na serwach
2024-11-30 poprawki ciag dalszy
2024-11-30 chyba dziala, naprawiono blad dziwnej pozycji, ostatni commit przed wlaczeniem silnikow
2024-11-30 udalo sie uruchomić robota tak żeby ruszal, pozycje tez poprawne
2024-11-30 robot chodzi ale ma dziwne bledy jakis progres jest
2024-11-30 robot chodzi do przodu i do tylu
2024-12-02 poprawiono schematy elektroniczne
2024-12-04 robot skrecaaaaaaaaaaa
2024-12-04 poprawiono but
2024-12-05 dodano obrazek
2024-12-08 dostrojenie chodu
2024-12-08 skrecanie w miejscu i naprawiono minusy predkosci
2024-12-08 zmiany w poz. tran, walk, robot off
2024-12-20 dodano kod do generowania csv
2024-12-20 wygenerowano pliki csv
2025-04-04 utworzono skrypt ustawiania zerowych pozycji
